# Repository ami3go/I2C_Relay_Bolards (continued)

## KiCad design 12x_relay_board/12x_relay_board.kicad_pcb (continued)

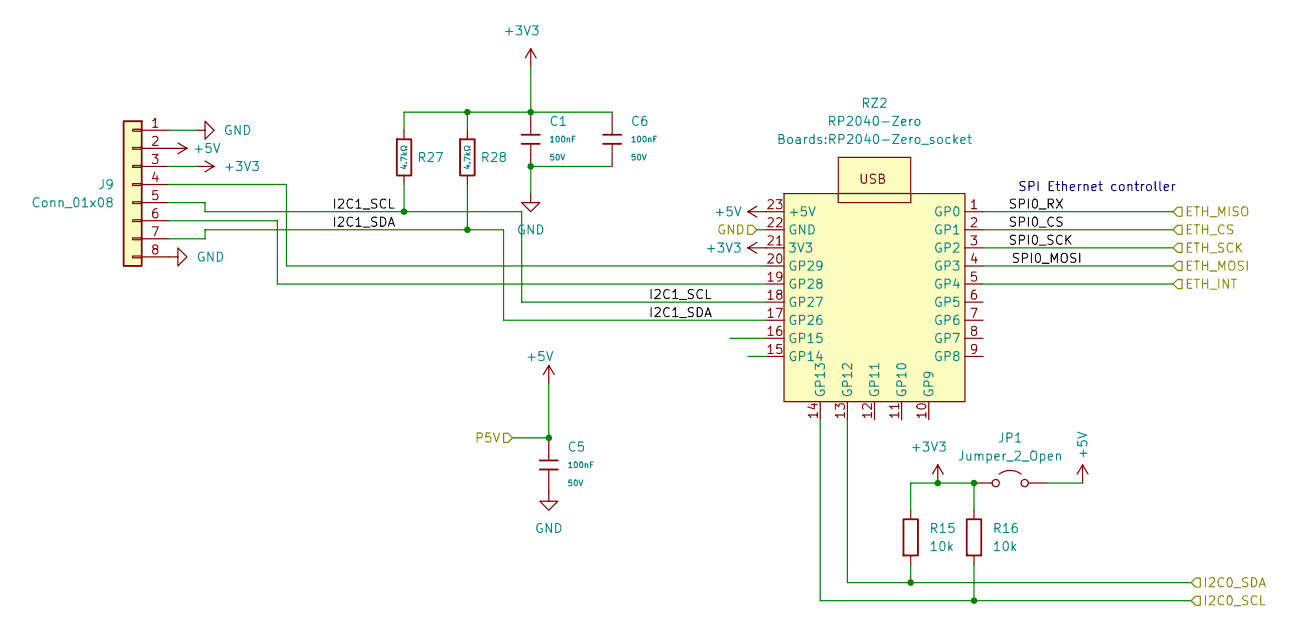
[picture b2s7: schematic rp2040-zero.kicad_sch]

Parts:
C1, C5, C6: 100nF; C_0603; Voltage Rated 50V; Tolerance ±10%; Part CC0603KRX7R9BB104; LCSC C14663
J9: Conn_01x08; PinHeader_2x04_P2.54mm_Vertical
JP1: Jumper_2_Open
R15, R16: 10k_0603; R_0603; Part Number RC0603FR-0710KL; JLCPCB ID C25804
R27, R28: 4.7kΩ; R_0603; Overload Voltage (Max) 75V; Tolerance ±1%; Part 0603WAF4701T5E; LCSC C23162
RZ2: RP2040-Zero; RP2040-Zero_socket

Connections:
+5V: C5.1, J9.2, RZ2.23 (+5V); also elsewhere on the board
/ETH/INT: RZ2.5 (GP4); also elsewhere on the board
/Untitled Sheet/I2C1_SCL: J9.5, R27.2, RZ2.18 (GP27)
/Untitled Sheet/I2C1_SDA: J9.7, R28.2, RZ2.17 (GP26)
/Untitled Sheet/SPI0_CS: RZ2.2 (GP1); also elsewhere on the board
/Untitled Sheet/SPI0_MOSI: RZ2.4 (GP3); also elsewhere on the board
/Untitled Sheet/SPI0_RX: RZ2.1 (GP0); also elsewhere on the board
/Untitled Sheet/SPI0_SCK: RZ2.3 (GP2); also elsewhere on the board
/conrol/SCL: R16.2, RZ2.14 (GP13); also elsewhere on the board
/conrol/SDA: R15.2, RZ2.13 (GP12); also elsewhere on the board
GND: C1.2, C5.2, C6.2, J9.1, J9.8, RZ2.22 (GND); also elsewhere on the board
unnamed: J9.4, RZ2.20 (GP29)
unnamed: J9.6, RZ2.19 (GP28)

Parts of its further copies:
R5: 4.7kΩ; R_0603; Overload Voltage (Max) 75V; Tolerance ±1%; Part 0603WAF4701T5E; LCSC C23162

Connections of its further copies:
unnamed 94: R5.2; also elsewhere on the board
PWR_12V: R5.1; also elsewhere on the board

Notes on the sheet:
SPI Ethernet controller

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
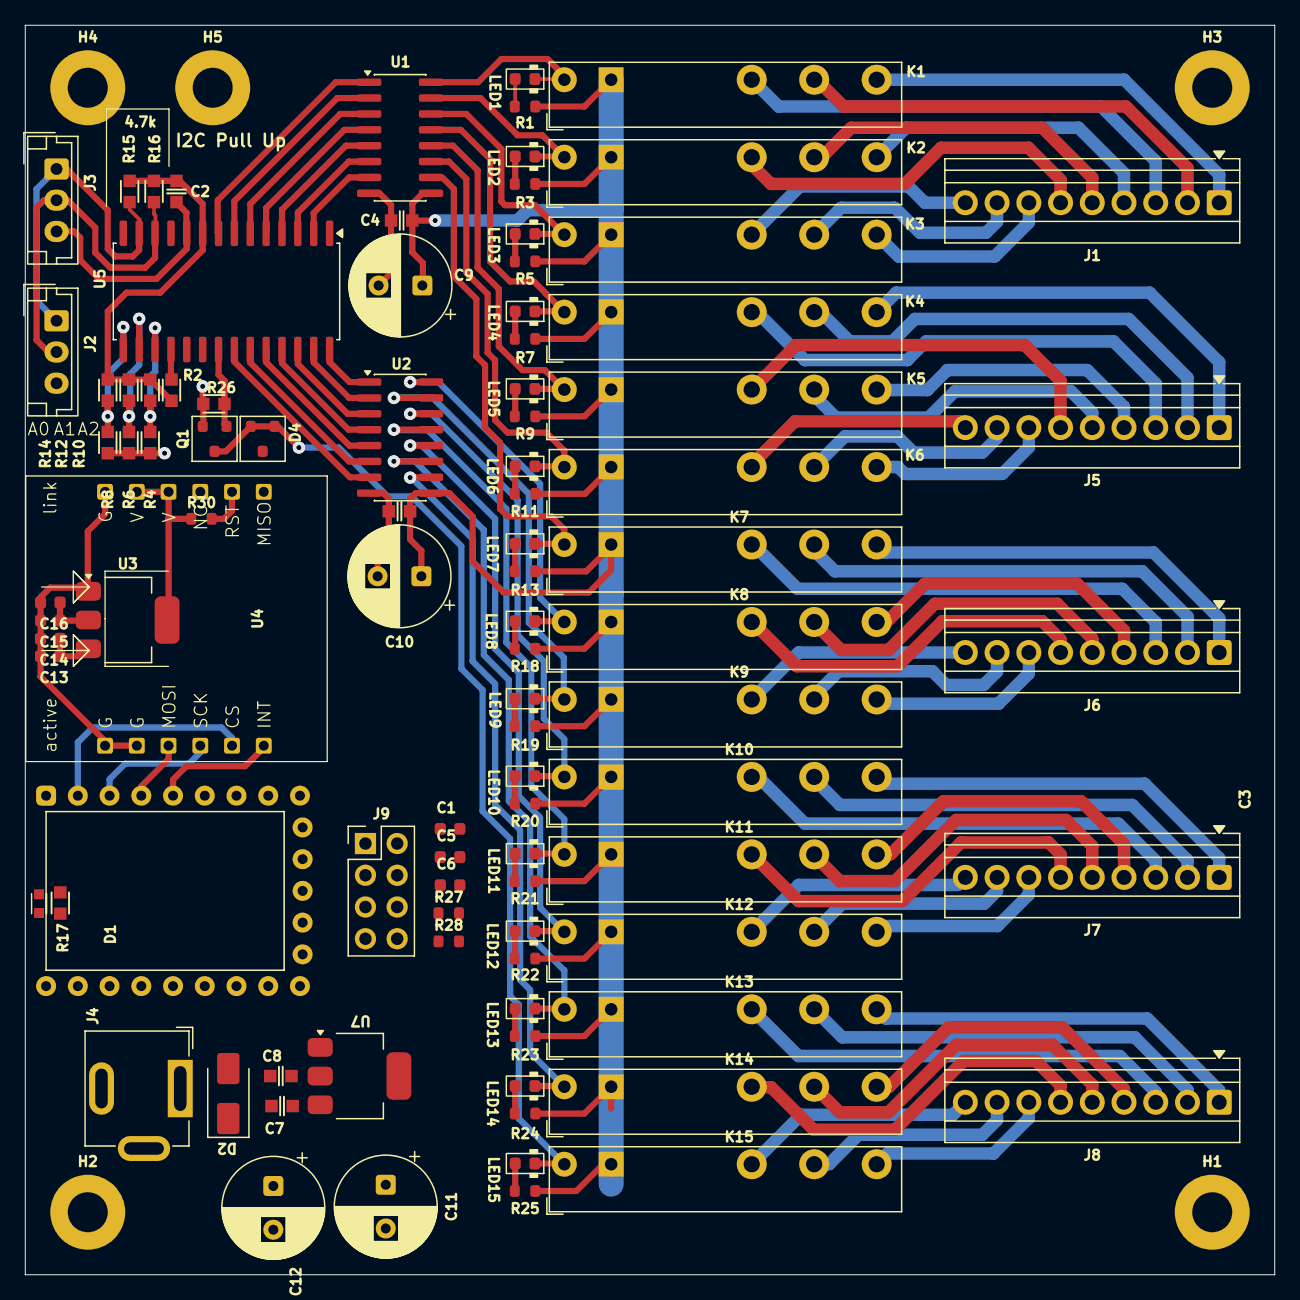
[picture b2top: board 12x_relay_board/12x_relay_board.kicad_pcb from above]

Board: 2 copper layers, 100.0 x 100.0 mm, 100 parts (0 on the bottom side), 115 nets.

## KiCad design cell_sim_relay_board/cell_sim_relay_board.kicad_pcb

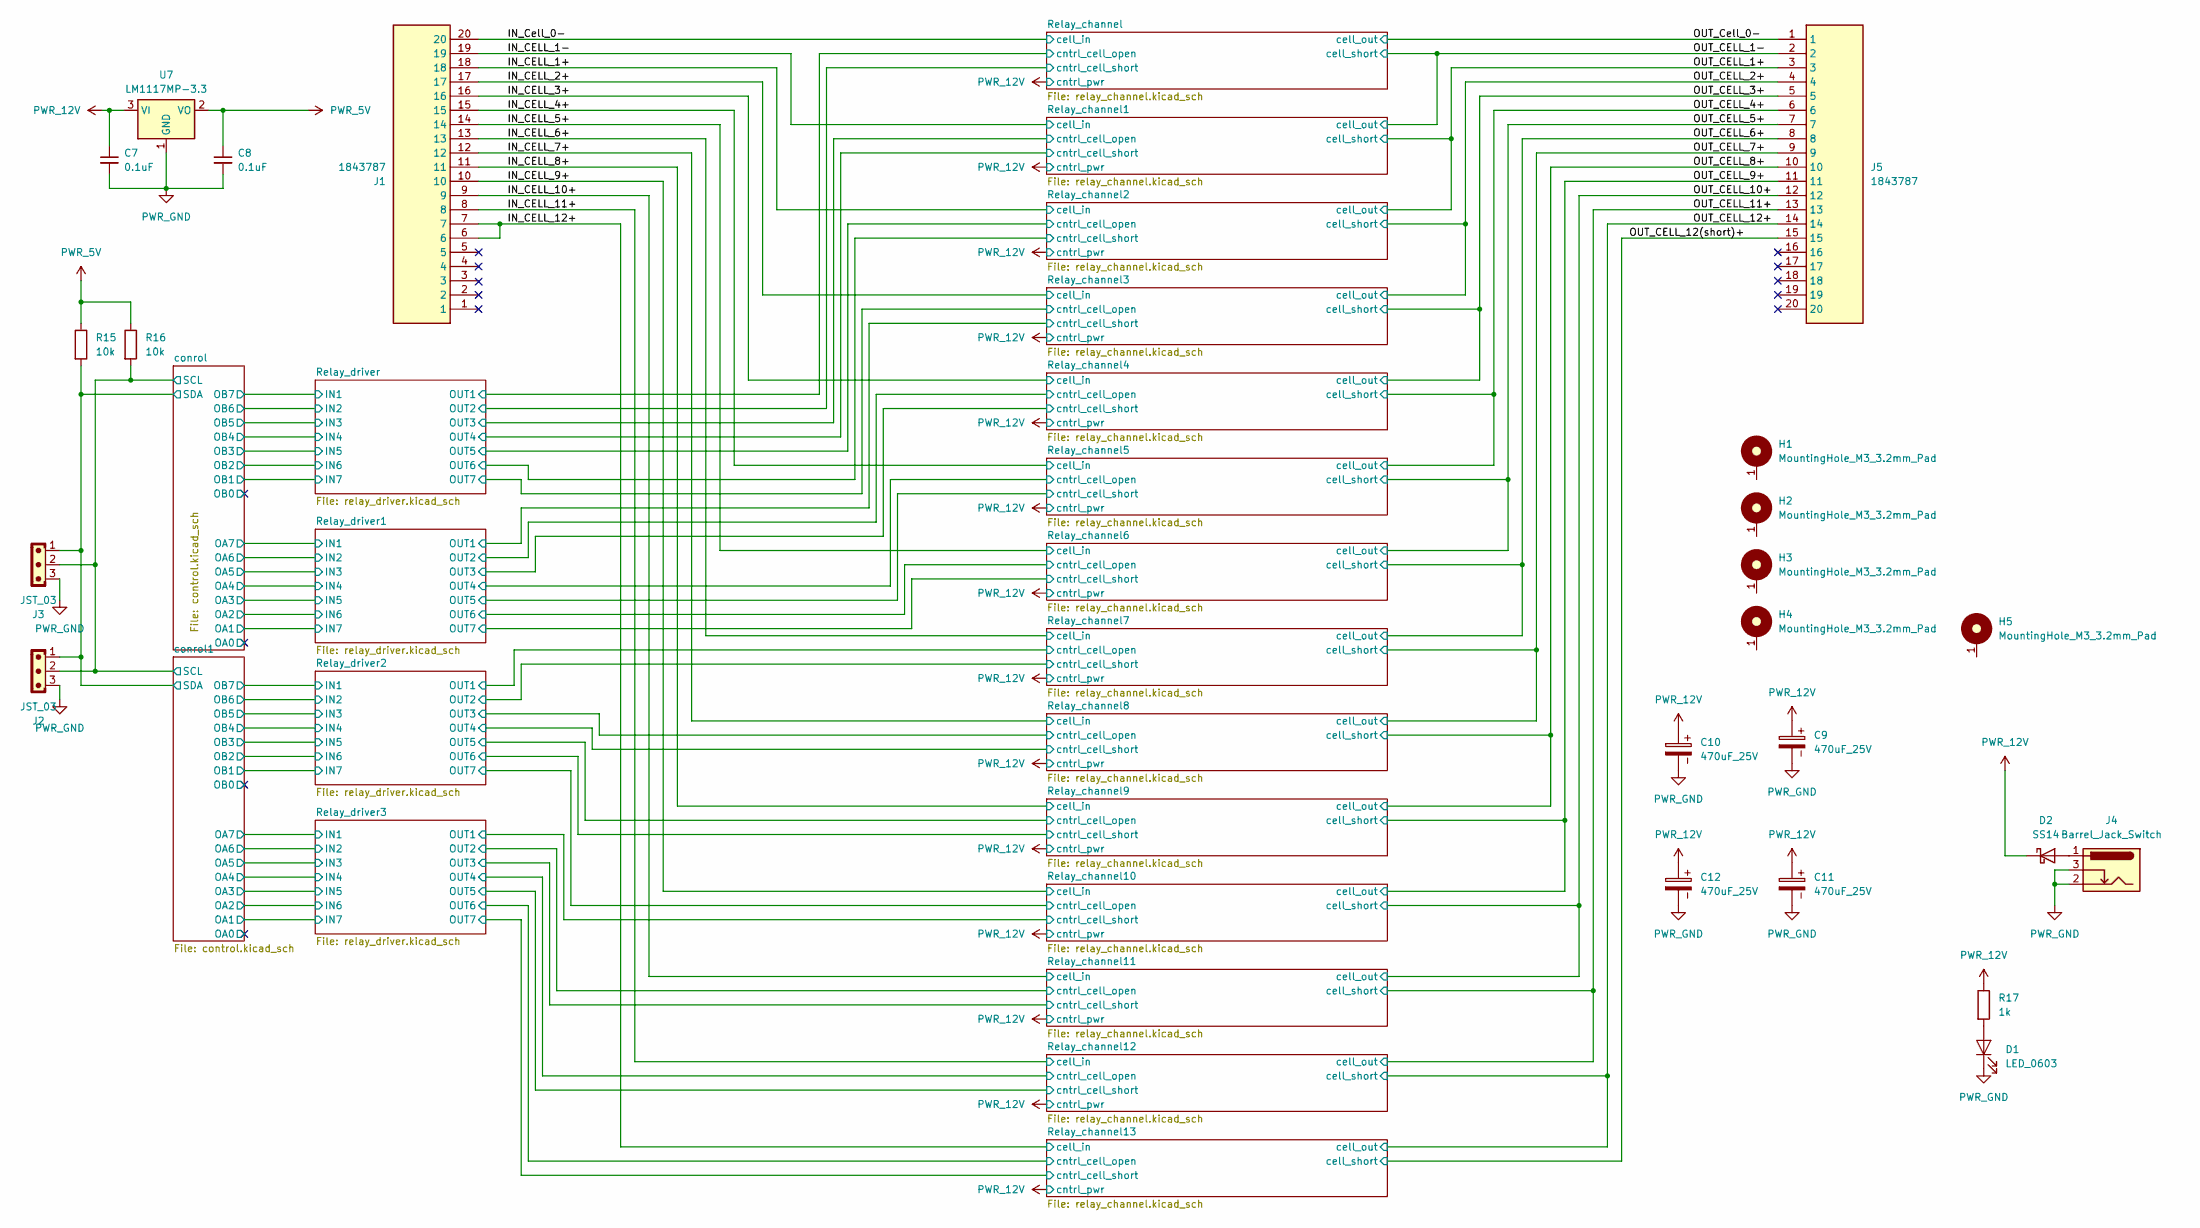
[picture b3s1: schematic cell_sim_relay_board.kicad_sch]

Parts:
C7, C8: 100nF_0603_16V; C_0603; Part Number 0603YC104KAT2A; JLCPCB ID C14663
C9, C10, C11, C12: 470uF_25V; CP_Radial_D8.0mm_P3.50mm
D1: LED_0603
D2: SS14; D_SMA
H1, H2, H3, H4, H5: MountingHole_M3_3.2mm_Pad; MountingHole_3.2mm_Pad
J1, J5: 1843787; 39502-1020_1X20; Mouser Part Number 651-1843787
J2, J3: JST_03; JST_EH_B3B-EH-A_1x03_P2.50mm_Vertical
J4: Barrel_Jack_Switch; BarrelJack_GCT_DCJ200-10-A_Horizontal
R15, R16: 10k_0603; R_0603; Part Number RC0603FR-0710KL; JLCPCB ID C25804
R17: 1k_0603; R_0603; Part Number RC0603FR-071KL; JLCPCB ID C21190
U7: LM1117MP-3.3; SOT-223-3_TabPin2

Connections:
/IN_CELL_1+: J1.18; also elsewhere on the board
/IN_CELL_1-: J1.19; also elsewhere on the board
/IN_CELL_2+: J1.17; also elsewhere on the board
/IN_CELL_3+: J1.16; also elsewhere on the board
/IN_CELL_4+: J1.15; also elsewhere on the board
/IN_CELL_5+: J1.14; also elsewhere on the board
/IN_CELL_6+: J1.13; also elsewhere on the board
/IN_CELL_7+: J1.12; also elsewhere on the board
/IN_CELL_8+: J1.11; also elsewhere on the board
/IN_CELL_9+: J1.10; also elsewhere on the board
/IN_CELL_10+: J1.9; also elsewhere on the board
/IN_CELL_11+: J1.8; also elsewhere on the board
/IN_CELL_12+: J1.6, J1.7; also elsewhere on the board
/IN_Cell_0-: J1.20; also elsewhere on the board
/OUT_CELL_1+: J5.3; also elsewhere on the board
/OUT_CELL_1-: J5.2; also elsewhere on the board
/OUT_CELL_2+: J5.4; also elsewhere on the board
/OUT_CELL_3+: J5.5; also elsewhere on the board
/OUT_CELL_4+: J5.6; also elsewhere on the board
/OUT_CELL_5+: J5.7; also elsewhere on the board
/OUT_CELL_6+: J5.8; also elsewhere on the board
/OUT_CELL_7+: J5.9; also elsewhere on the board
/OUT_CELL_8+: J5.10; also elsewhere on the board
/OUT_CELL_9+: J5.11; also elsewhere on the board
/OUT_CELL_10+: J5.12; also elsewhere on the board
/OUT_CELL_11+: J5.13; also elsewhere on the board
/OUT_CELL_12(short)+: J5.15; also elsewhere on the board
/OUT_CELL_12+: J5.14; also elsewhere on the board
/OUT_Cell_0-: J5.1; also elsewhere on the board
/conrol/SCL: J2.2, J3.2, R16.2; also elsewhere on the board
/conrol/SDA: J2.1, J3.1, R15.2; also elsewhere on the board
unnamed: D1.2 (A), R17.2
unnamed: D2.2 (A), J4.1
PWR_5V: C8.1, R15.1, R16.1, U7.2 (VO); also elsewhere on the board
PWR_12V: C7.1, C9.1, C10.1, C11.1, C12.1, D2.1 (K), R17.1, U7.3 (VI); also elsewhere on the board
PWR_GND: C7.2, C8.2, C9.2, C10.2, C11.2, C12.2, D1.1 (K), J2.3, J3.3, J4.2, J4.3, U7.1 (GND); also elsewhere on the board

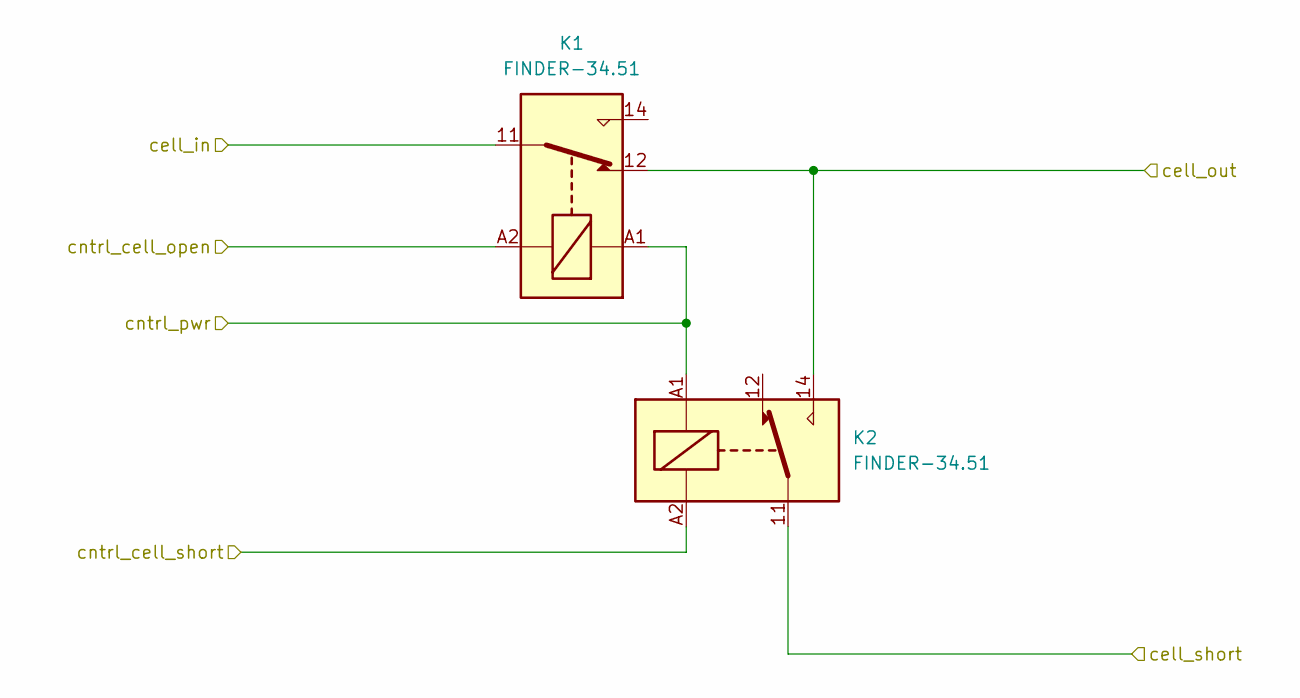
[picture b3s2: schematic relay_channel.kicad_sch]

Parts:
K1, K2: FINDER-34.51; Relay_SPDT_Finder_34.51_Vertical

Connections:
/IN_Cell_0-: K1.11; also elsewhere on the board
/OUT_CELL_1-: K2.11; also elsewhere on the board
/OUT_Cell_0-: K1.12, K2.14; also elsewhere on the board
/Relay_channel/cntrl_cell_open: K1.A2; also elsewhere on the board
/Relay_channel/cntrl_cell_short: K2.A2; also elsewhere on the board
PWR_12V: K1.A1, K2.A1; also elsewhere on the board

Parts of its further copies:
K3, K4, K5, K6, K7, K8, K9, K10, K11, K12, K13, K14, K15, K16, K17, K18, K19, K20, K21, K22, K23, K24, K25, K26, K27, K28: FINDER-34.51; Relay_SPDT_Finder_34.51_Vertical

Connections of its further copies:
/IN_CELL_1+: K5.11; also elsewhere on the board
/IN_CELL_1-: K3.11; also elsewhere on the board
/IN_CELL_2+: K7.11; also elsewhere on the board
/IN_CELL_3+: K9.11; also elsewhere on the board
/IN_CELL_4+: K11.11; also elsewhere on the board
/IN_CELL_5+: K13.11; also elsewhere on the board
/IN_CELL_6+: K15.11; also elsewhere on the board
/IN_CELL_7+: K17.11; also elsewhere on the board
/IN_CELL_8+: K19.11; also elsewhere on the board
/IN_CELL_9+: K21.11; also elsewhere on the board
/IN_CELL_10+: K23.11; also elsewhere on the board
/IN_CELL_11+: K25.11; also elsewhere on the board
/IN_CELL_12+: K27.11; also elsewhere on the board
/OUT_CELL_1+: K4.11, K5.12, K6.14; also elsewhere on the board
/OUT_CELL_1-: K3.12, K4.14; also elsewhere on the board
/OUT_CELL_2+: K6.11, K7.12, K8.14; also elsewhere on the board
/OUT_CELL_3+: K8.11, K9.12, K10.14; also elsewhere on the board
/OUT_CELL_4+: K10.11, K11.12, K12.14; also elsewhere on the board
/OUT_CELL_5+: K12.11, K13.12, K14.14; also elsewhere on the board
/OUT_CELL_6+: K14.11, K15.12, K16.14; also elsewhere on the board
/OUT_CELL_7+: K16.11, K17.12, K18.14; also elsewhere on the board
/OUT_CELL_8+: K18.11, K19.12, K20.14; also elsewhere on the board
/OUT_CELL_9+: K20.11, K21.12, K22.14; also elsewhere on the board
/OUT_CELL_10+: K22.11, K23.12, K24.14; also elsewhere on the board
/OUT_CELL_11+: K24.11, K25.12, K26.14; also elsewhere on the board
/OUT_CELL_12(short)+: K28.11; also elsewhere on the board
/OUT_CELL_12+: K26.11, K27.12, K28.14; also elsewhere on the board
/Relay_channel1/cntrl_cell_open: K3.A2; also elsewhere on the board
/Relay_channel1/cntrl_cell_short: K4.A2; also elsewhere on the board
/Relay_channel2/cntrl_cell_open: K5.A2; also elsewhere on the board
/Relay_channel2/cntrl_cell_short: K6.A2; also elsewhere on the board
/Relay_channel3/cntrl_cell_open: K7.A2; also elsewhere on the board
/Relay_channel3/cntrl_cell_short: K8.A2; also elsewhere on the board
/Relay_channel4/cntrl_cell_open: K9.A2; also elsewhere on the board
/Relay_channel4/cntrl_cell_short: K10.A2; also elsewhere on the board
/Relay_channel5/cntrl_cell_open: K11.A2; also elsewhere on the board
/Relay_channel5/cntrl_cell_short: K12.A2; also elsewhere on the board
/Relay_channel6/cntrl_cell_open: K13.A2; also elsewhere on the board
/Relay_channel6/cntrl_cell_short: K14.A2; also elsewhere on the board
/Relay_channel7/cntrl_cell_open: K15.A2; also elsewhere on the board
/Relay_channel7/cntrl_cell_short: K16.A2; also elsewhere on the board
/Relay_channel8/cntrl_cell_open: K17.A2; also elsewhere on the board
/Relay_channel8/cntrl_cell_short: K18.A2; also elsewhere on the board
/Relay_channel9/cntrl_cell_open: K19.A2; also elsewhere on the board
/Relay_channel9/cntrl_cell_short: K20.A2; also elsewhere on the board
/Relay_channel10/cntrl_cell_open: K21.A2; also elsewhere on the board
/Relay_channel10/cntrl_cell_short: K22.A2; also elsewhere on the board
/Relay_channel11/cntrl_cell_open: K23.A2; also elsewhere on the board
/Relay_channel11/cntrl_cell_short: K24.A2; also elsewhere on the board
/Relay_channel12/cntrl_cell_open: K25.A2; also elsewhere on the board
/Relay_channel12/cntrl_cell_short: K26.A2; also elsewhere on the board
/Relay_channel13/cntrl_cell_open: K27.A2; also elsewhere on the board
/Relay_channel13/cntrl_cell_short: K28.A2; also elsewhere on the board
PWR_12V: K3.A1, K4.A1, K5.A1, K6.A1, K7.A1, K8.A1, K9.A1, K10.A1, K11.A1, K12.A1, K13.A1, K14.A1, K15.A1, K16.A1, K17.A1, K18.A1, K19.A1, K20.A1, K21.A1, K22.A1, K23.A1, K24.A1, K25.A1, K26.A1, K27.A1, K28.A1; also elsewhere on the board

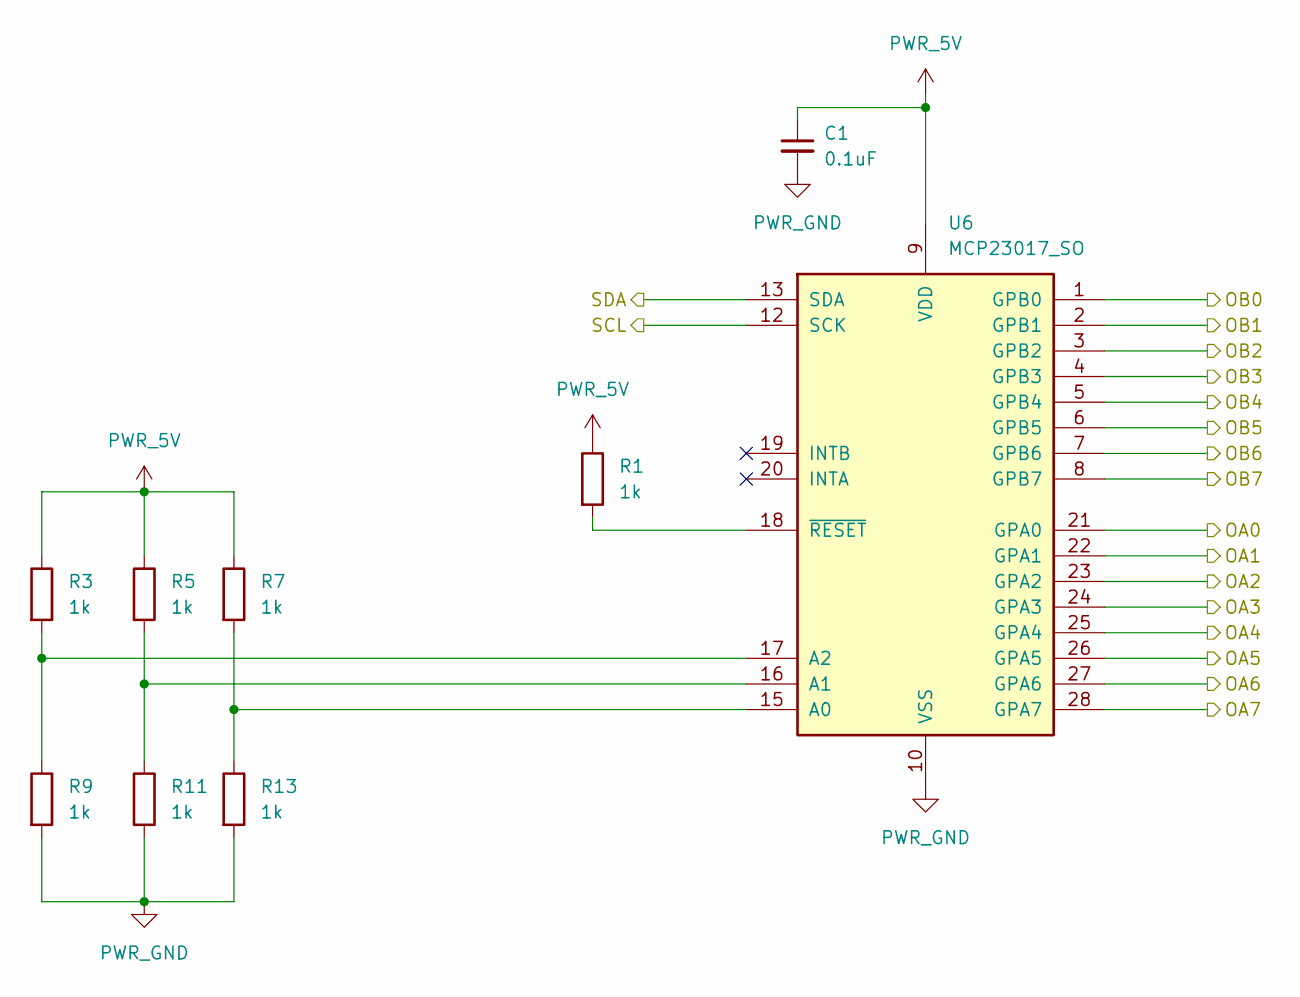
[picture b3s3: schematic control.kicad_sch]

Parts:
C1: 100nF_0603_16V; C_0603; Part Number 0603YC104KAT2A; JLCPCB ID C14663
R1, R3, R5, R7, R9, R11, R13: 1k_0603; R_0603; Part Number RC0603FR-071KL; JLCPCB ID C21190
U6: MCP23017_SO; SOIC-28W_7.5x17.9mm_P1.27mm

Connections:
/Relay_driver2/IN1: U6.8 (GPB7); also elsewhere on the board
/Relay_driver2/IN2: U6.7 (GPB6); also elsewhere on the board
/Relay_driver2/IN3: U6.6 (GPB5); also elsewhere on the board
/Relay_driver2/IN4: U6.5 (GPB4); also elsewhere on the board
/Relay_driver2/IN5: U6.4 (GPB3); also elsewhere on the board
/Relay_driver2/IN6: U6.3 (GPB2); also elsewhere on the board
/Relay_driver2/IN7: U6.2 (GPB1); also elsewhere on the board
/Relay_driver3/IN1: U6.28 (GPA7); also elsewhere on the board
/Relay_driver3/IN2: U6.27 (GPA6); also elsewhere on the board
/Relay_driver3/IN3: U6.26 (GPA5); also elsewhere on the board
/Relay_driver3/IN4: U6.25 (GPA4); also elsewhere on the board
/Relay_driver3/IN5: U6.24 (GPA3); also elsewhere on the board
/Relay_driver3/IN6: U6.23 (GPA2); also elsewhere on the board
/Relay_driver3/IN7: U6.22 (GPA1); also elsewhere on the board
/conrol1/OA0: U6.21 (GPA0)
/conrol1/OB0: U6.1 (GPB0)
/conrol/SCL: U6.12 (SCK); also elsewhere on the board
/conrol/SDA: U6.13 (SDA); also elsewhere on the board
unnamed: R7.2, R13.1, U6.15 (A0)
unnamed: R5.2, R11.1, U6.16 (A1)
unnamed: R3.2, R9.1, U6.17 (A2)
unnamed: R1.2, U6.18 (~RESET)
PWR_5V: C1.1, R1.1, R3.1, R5.1, R7.1, U6.9 (VDD); also elsewhere on the board
PWR_GND: C1.2, R9.2, R11.2, R13.2, U6.10 (VSS); also elsewhere on the board

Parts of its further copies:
C2: 100nF_0603_16V; C_0603; Part Number 0603YC104KAT2A; JLCPCB ID C14663
R2, R4, R6, R8, R10, R12, R14: 1k_0603; R_0603; Part Number RC0603FR-071KL; JLCPCB ID C21190
U5: MCP23017_SO; SOIC-28W_7.5x17.9mm_P1.27mm

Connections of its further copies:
/Relay_driver1/IN1: U5.28 (GPA7); also elsewhere on the board
/Relay_driver1/IN2: U5.27 (GPA6); also elsewhere on the board
/Relay_driver1/IN3: U5.26 (GPA5); also elsewhere on the board
/Relay_driver1/IN4: U5.25 (GPA4); also elsewhere on the board
/Relay_driver1/IN5: U5.24 (GPA3); also elsewhere on the board
/Relay_driver1/IN6: U5.23 (GPA2); also elsewhere on the board
/Relay_driver1/IN7: U5.22 (GPA1); also elsewhere on the board
/Relay_driver/IN1: U5.8 (GPB7); also elsewhere on the board
/Relay_driver/IN2: U5.7 (GPB6); also elsewhere on the board
/Relay_driver/IN3: U5.6 (GPB5); also elsewhere on the board
/Relay_driver/IN4: U5.5 (GPB4); also elsewhere on the board
/Relay_driver/IN5: U5.4 (GPB3); also elsewhere on the board
/Relay_driver/IN6: U5.3 (GPB2); also elsewhere on the board
/Relay_driver/IN7: U5.2 (GPB1); also elsewhere on the board
/conrol/OA0: U5.21 (GPA0)
/conrol/OB0: U5.1 (GPB0)
/conrol/SCL: U5.12 (SCK); also elsewhere on the board
/conrol/SDA: U5.13 (SDA); also elsewhere on the board
unnamed: R8.2, R14.1, U5.15 (A0)
unnamed: R6.2, R12.1, U5.16 (A1)
unnamed: R4.2, R10.1, U5.17 (A2)
unnamed: R2.2, U5.18 (~RESET)
PWR_5V: C2.1, R2.1, R4.1, R6.1, R8.1, U5.9 (VDD); also elsewhere on the board
PWR_GND: C2.2, R10.2, R12.2, R14.2, U5.10 (VSS); also elsewhere on the board

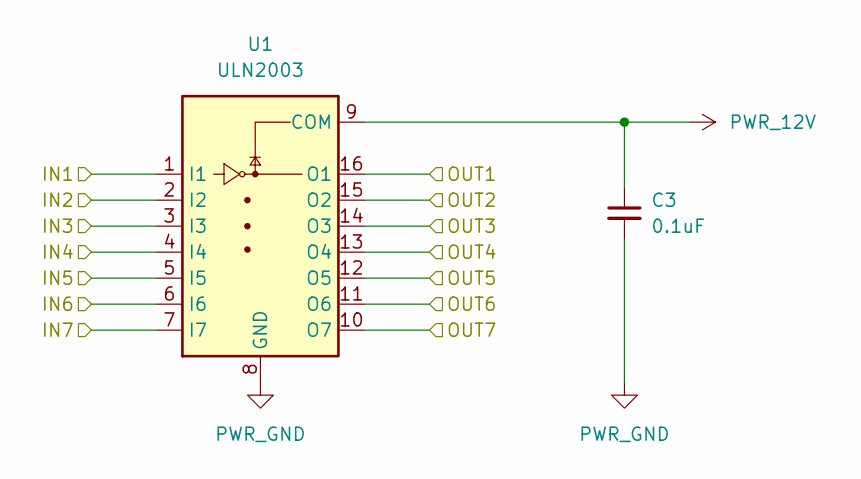
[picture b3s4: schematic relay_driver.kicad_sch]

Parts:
C3: 100nF_0603_16V; C_0603; Part Number 0603YC104KAT2A; JLCPCB ID C14663
U1: ULN2003; SOIC-16_3.9x9.9mm_P1.27mm

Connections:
/Relay_channel1/cntrl_cell_open: U1.14 (O3); also elsewhere on the board
/Relay_channel1/cntrl_cell_short: U1.13 (O4); also elsewhere on the board
/Relay_channel2/cntrl_cell_open: U1.12 (O5); also elsewhere on the board
/Relay_channel2/cntrl_cell_short: U1.11 (O6); also elsewhere on the board
/Relay_channel3/cntrl_cell_open: U1.10 (O7); also elsewhere on the board
/Relay_channel/cntrl_cell_open: U1.16 (O1); also elsewhere on the board
/Relay_channel/cntrl_cell_short: U1.15 (O2); also elsewhere on the board
/Relay_driver/IN1: U1.1 (I1); also elsewhere on the board
/Relay_driver/IN2: U1.2 (I2); also elsewhere on the board
/Relay_driver/IN3: U1.3 (I3); also elsewhere on the board
/Relay_driver/IN4: U1.4 (I4); also elsewhere on the board
/Relay_driver/IN5: U1.5 (I5); also elsewhere on the board
/Relay_driver/IN6: U1.6 (I6); also elsewhere on the board
/Relay_driver/IN7: U1.7 (I7); also elsewhere on the board
PWR_12V: C3.1, U1.9 (COM); also elsewhere on the board
PWR_GND: C3.2, U1.8 (GND); also elsewhere on the board

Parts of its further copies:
C4, C5, C6: 100nF_0603_16V; C_0603; Part Number 0603YC104KAT2A; JLCPCB ID C14663
U2, U3, U4: ULN2003; SOIC-16_3.9x9.9mm_P1.27mm

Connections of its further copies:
/Relay_channel3/cntrl_cell_short: U2.16 (O1); also elsewhere on the board
/Relay_channel4/cntrl_cell_open: U2.15 (O2); also elsewhere on the board
/Relay_channel4/cntrl_cell_short: U2.14 (O3); also elsewhere on the board
/Relay_channel5/cntrl_cell_open: U2.13 (O4); also elsewhere on the board
/Relay_channel5/cntrl_cell_short: U2.12 (O5); also elsewhere on the board
/Relay_channel6/cntrl_cell_open: U2.11 (O6); also elsewhere on the board
/Relay_channel6/cntrl_cell_short: U2.10 (O7); also elsewhere on the board
/Relay_channel7/cntrl_cell_open: U3.16 (O1); also elsewhere on the board
/Relay_channel7/cntrl_cell_short: U3.15 (O2); also elsewhere on the board
/Relay_channel8/cntrl_cell_open: U3.14 (O3); also elsewhere on the board
/Relay_channel8/cntrl_cell_short: U3.13 (O4); also elsewhere on the board
/Relay_channel9/cntrl_cell_open: U3.12 (O5); also elsewhere on the board
/Relay_channel9/cntrl_cell_short: U3.11 (O6); also elsewhere on the board
/Relay_channel10/cntrl_cell_open: U3.10 (O7); also elsewhere on the board
/Relay_channel10/cntrl_cell_short: U4.16 (O1); also elsewhere on the board
/Relay_channel11/cntrl_cell_open: U4.15 (O2); also elsewhere on the board
/Relay_channel11/cntrl_cell_short: U4.14 (O3); also elsewhere on the board
/Relay_channel12/cntrl_cell_open: U4.13 (O4); also elsewhere on the board
/Relay_channel12/cntrl_cell_short: U4.12 (O5); also elsewhere on the board
/Relay_channel13/cntrl_cell_open: U4.11 (O6); also elsewhere on the board
/Relay_channel13/cntrl_cell_short: U4.10 (O7); also elsewhere on the board
/Relay_driver1/IN1: U2.1 (I1); also elsewhere on the board
/Relay_driver1/IN2: U2.2 (I2); also elsewhere on the board
/Relay_driver1/IN3: U2.3 (I3); also elsewhere on the board
/Relay_driver1/IN4: U2.4 (I4); also elsewhere on the board
/Relay_driver1/IN5: U2.5 (I5); also elsewhere on the board
/Relay_driver1/IN6: U2.6 (I6); also elsewhere on the board
/Relay_driver1/IN7: U2.7 (I7); also elsewhere on the board
/Relay_driver2/IN1: U3.1 (I1); also elsewhere on the board
/Relay_driver2/IN2: U3.2 (I2); also elsewhere on the board
/Relay_driver2/IN3: U3.3 (I3); also elsewhere on the board
/Relay_driver2/IN4: U3.4 (I4); also elsewhere on the board
/Relay_driver2/IN5: U3.5 (I5); also elsewhere on the board
/Relay_driver2/IN6: U3.6 (I6); also elsewhere on the board
/Relay_driver2/IN7: U3.7 (I7); also elsewhere on the board
/Relay_driver3/IN1: U4.1 (I1); also elsewhere on the board
/Relay_driver3/IN2: U4.2 (I2); also elsewhere on the board
/Relay_driver3/IN3: U4.3 (I3); also elsewhere on the board
/Relay_driver3/IN4: U4.4 (I4); also elsewhere on the board
/Relay_driver3/IN5: U4.5 (I5); also elsewhere on the board
/Relay_driver3/IN6: U4.6 (I6); also elsewhere on the board
/Relay_driver3/IN7: U4.7 (I7); also elsewhere on the board
PWR_12V: C4.1, C5.1, C6.1, U2.9 (COM), U3.9 (COM), U4.9 (COM); also elsewhere on the board
PWR_GND: C4.2, C5.2, C6.2, U2.8 (GND), U3.8 (GND), U4.8 (GND); also elsewhere on the board

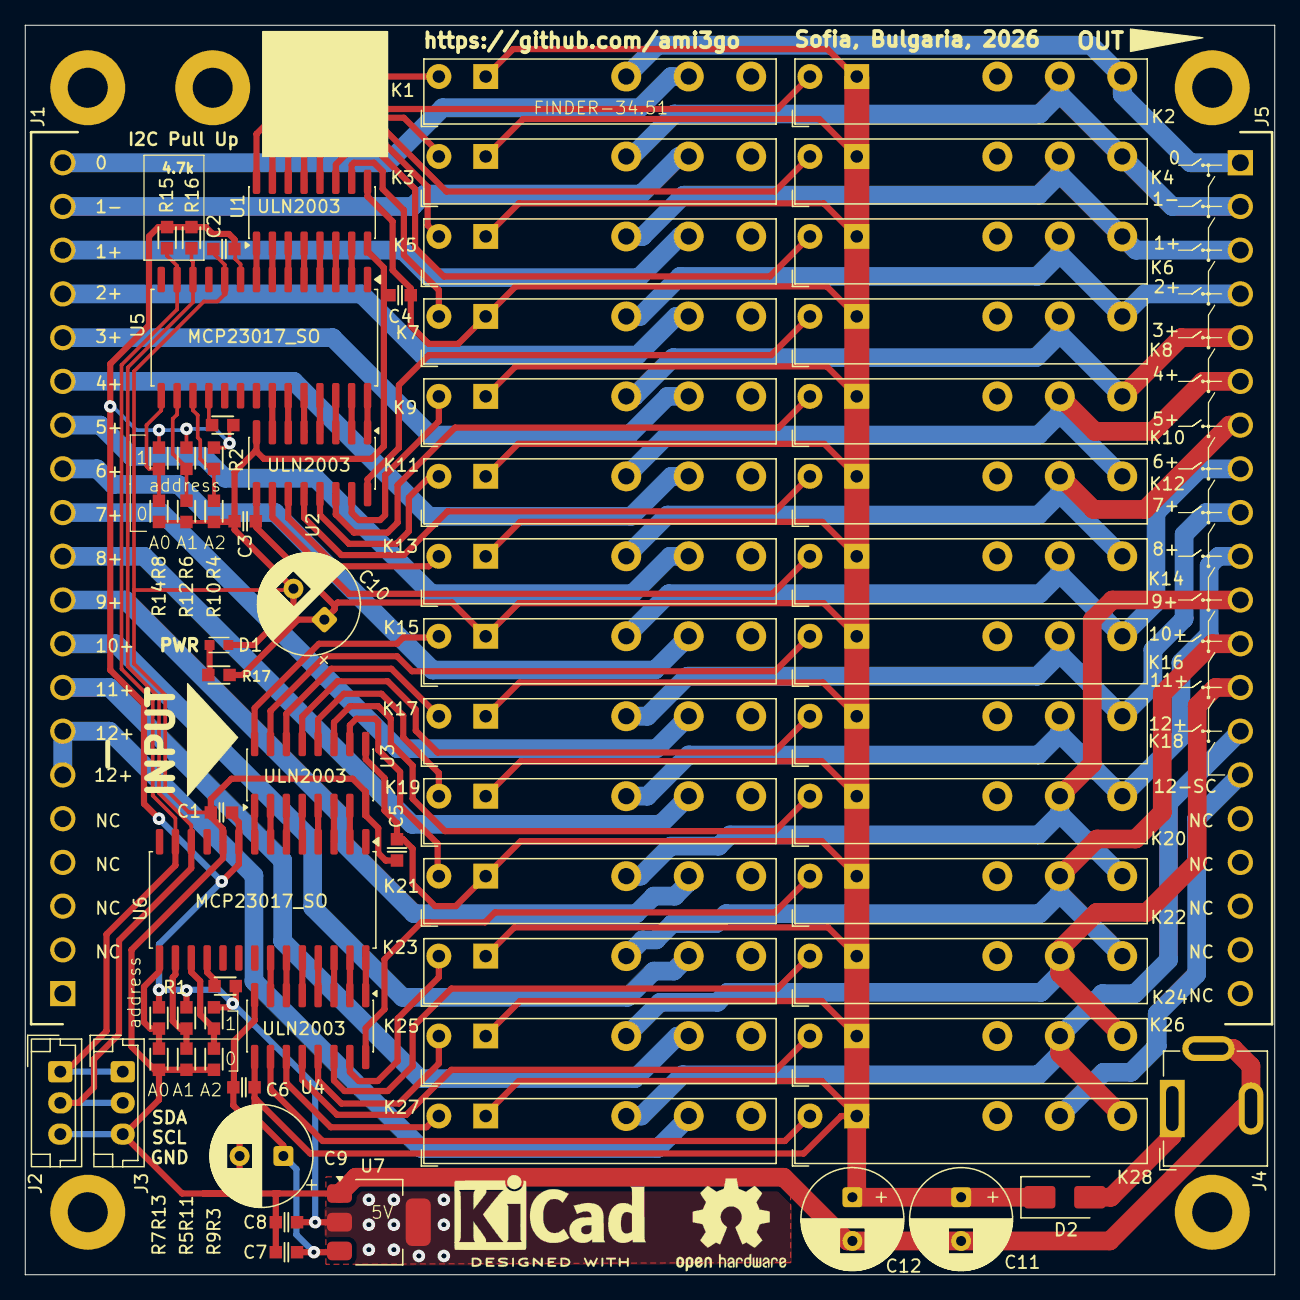
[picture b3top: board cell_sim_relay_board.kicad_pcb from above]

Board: 2 copper layers, 100.0 x 100.0 mm, 76 parts (0 on the bottom side), 100 nets.

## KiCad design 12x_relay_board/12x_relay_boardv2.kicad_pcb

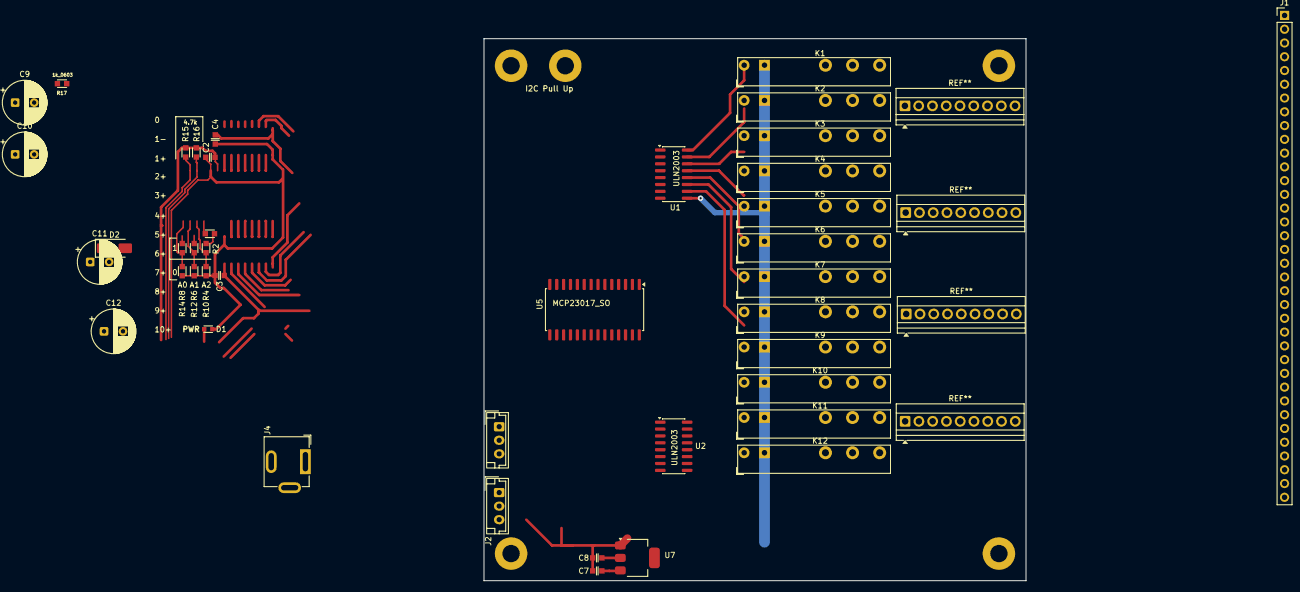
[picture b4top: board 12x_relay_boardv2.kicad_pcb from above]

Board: 2 copper layers, 100.0 x 100.0 mm, 46 parts (0 on the bottom side), 73 nets.

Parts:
C2, C3, C4, C7, C8: 100nF_0603_16V; C_0603
C9, C10, C11, C12: 470uF_25V; CP_Radial_D8.0mm_P3.50mm
D1: LED_0603
D2: SS14; D_SMA
H1, H2, H3, H4, H5: MountingHole_M3_3.2mm_Pad; MountingHole_3.2mm_Pad
J1: Conn_01x36_MountingPin; PinHeader_1x36_P2.54mm_Vertical
J2, J3: JST_03; JST_EH_B3B-EH-A_1x03_P2.50mm_Vertical
J4: Barrel_Jack_Switch; BarrelJack_GCT_DCJ200-10-A_Horizontal
K1, K2, K3, K4, K5, K6, K7, K8, K9, K10, K11, K12: FINDER-34.51; Relay_SPDT_Finder_34.51_Vertical
R2, R4, R6, R8, R10, R12, R14, R17: 1k_0603; R_0603
R15, R16: 10k_0603; R_0603
U1, U2: ULN2003; SOIC-16_3.9x9.9mm_P1.27mm
U5: MCP23017_SO; SOIC-28W_7.5x17.9mm_P1.27mm
U7: LM1117MP-3.3; SOT-223-3_TabPin2

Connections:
/Relay_channel_1/COM: J1.2, K1.11
/Relay_channel_1/NC: J1.3, K1.12
/Relay_channel_1/NO: J1.1, K1.14
/Relay_channel_1/cntrl_A1: K1.A2, U1.16 (O1)
/Relay_channel_2/COM: J1.5, K2.11
/Relay_channel_2/NC: J1.4, K2.12
/Relay_channel_2/NO: J1.6, K2.14
/Relay_channel_2/cntrl_A1: K2.A2, U1.15 (O2)
/Relay_channel_3/COM: J1.8, K3.11
/Relay_channel_3/NC: J1.7, K3.12
/Relay_channel_3/NO: J1.9, K3.14
/Relay_channel_3/cntrl_A1: K3.A2, U1.14 (O3)
/Relay_channel_4/COM: J1.11, K4.11
/Relay_channel_4/NC: J1.10, K4.12
/Relay_channel_4/NO: J1.12, K4.14
/Relay_channel_4/cntrl_A1: K4.A2, U1.13 (O4)
/Relay_channel_5/COM: J1.14, K5.11
/Relay_channel_5/NC: J1.13, K5.12
/Relay_channel_5/NO: J1.15, K5.14
/Relay_channel_5/cntrl_A1: K5.A2, U1.12 (O5)
/Relay_channel_6/COM: J1.17, K6.11
/Relay_channel_6/NC: J1.16, K6.12
/Relay_channel_6/NO: J1.18, K6.14
/Relay_channel_6/cntrl_A1: K6.A2, U1.11 (O6)
/Relay_channel_7/COM: J1.20, K7.11
/Relay_channel_7/NC: J1.19, K7.12
/Relay_channel_7/NO: J1.21, K7.14
/Relay_channel_7/cntrl_A1: K7.A2, U2.16 (O1)
/Relay_channel_8/COM: J1.23, K8.11
/Relay_channel_8/NC: J1.22, K8.12
/Relay_channel_8/NO: J1.24, K8.14
/Relay_channel_8/cntrl_A1: K8.A2, U2.15 (O2)
/Relay_channel_9/COM: J1.26, K9.11
/Relay_channel_9/NC: J1.25, K9.12
/Relay_channel_9/NO: J1.27, K9.14
/Relay_channel_9/cntrl_A1: K9.A2, U2.14 (O3)
/Relay_channel_10/COM: J1.29, K10.11
/Relay_channel_10/NC: J1.28, K10.12
/Relay_channel_10/NO: J1.30, K10.14
/Relay_channel_10/cntrl_A1: K10.A2, U2.13 (O4)
/Relay_channel_11/COM: J1.32, K11.11
/Relay_channel_11/NC: J1.31, K11.12
/Relay_channel_11/NO: J1.33, K11.14
/Relay_channel_11/cntrl_A1: K11.A2, U2.12 (O5)
/Relay_channel_12/COM: J1.35, K12.11
/Relay_channel_12/NC: J1.34, K12.12
/Relay_channel_12/NO: J1.36, K12.14
/Relay_channel_12/cntrl_A1: K12.A2, U2.11 (O6)
/Relay_driver1/IN1: U2.1 (I1), U5.28 (GPA7)
/Relay_driver1/IN2: U2.2 (I2), U5.27 (GPA6)
/Relay_driver1/IN3: U2.3 (I3), U5.26 (GPA5)
/Relay_driver1/IN4: U2.4 (I4), U5.25 (GPA4)
/Relay_driver1/IN5: U2.5 (I5), U5.24 (GPA3)
/Relay_driver1/IN6: U2.6 (I6), U5.23 (GPA2)
/Relay_driver1/IN7: U2.7 (I7), U5.22 (GPA1)
/Relay_driver/IN1: U1.1 (I1), U5.8 (GPB7)
/Relay_driver/IN2: U1.2 (I2), U5.7 (GPB6)
/Relay_driver/IN3: U1.3 (I3), U5.6 (GPB5)
/Relay_driver/IN4: U1.4 (I4), U5.5 (GPB4)
/Relay_driver/IN5: U1.5 (I5), U5.4 (GPB3)
/Relay_driver/IN6: U1.6 (I6), U5.3 (GPB2)
/Relay_driver/IN7: U1.7 (I7), U5.2 (GPB1)
/conrol/SCL: J2.2, J3.2, R16.2, U5.12 (SCK)
/conrol/SDA: J2.1, J3.1, R15.2, U5.13 (SDA)
unnamed: D1.2 (A), R17.2
unnamed: D2.2 (A), J4.1
unnamed: R8.2, R14.1, U5.15 (A0)
unnamed: R6.2, R12.1, U5.16 (A1)
unnamed: R4.2, R10.1, U5.17 (A2)
unnamed: R2.2, U5.18 (~RESET)
PWR_5V: C2.1, C8.1, R2.1, R4.1, R6.1, R8.1, R15.1, R16.1, U5.9 (VDD), U7.2 (VO)
PWR_12V: C3.1, C4.1, C7.1, C9.1, C10.1, C11.1, C12.1, D2.1 (K), K1.A1, K2.A1, K3.A1, K4.A1, K5.A1, K6.A1, K7.A1, K8.A1, K9.A1, K10.A1, K11.A1, K12.A1, R17.1, U1.9 (COM), U2.9 (COM), U7.3 (VI)
PWR_GND: C2.2, C3.2, C4.2, C7.2, C8.2, C9.2, C10.2, C11.2, C12.2, D1.1 (K), J2.3, J3.3, J4.2, J4.3, R10.2, R12.2, R14.2, U1.8 (GND), U2.8 (GND), U5.10 (VSS), U7.1 (GND)

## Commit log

2026-04-21 clean up project
2026-04-21 backup
2026-04-21 clean up
